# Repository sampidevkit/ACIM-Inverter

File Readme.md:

# AC INDUCTION MOTOR - INVERTER BOARD V2

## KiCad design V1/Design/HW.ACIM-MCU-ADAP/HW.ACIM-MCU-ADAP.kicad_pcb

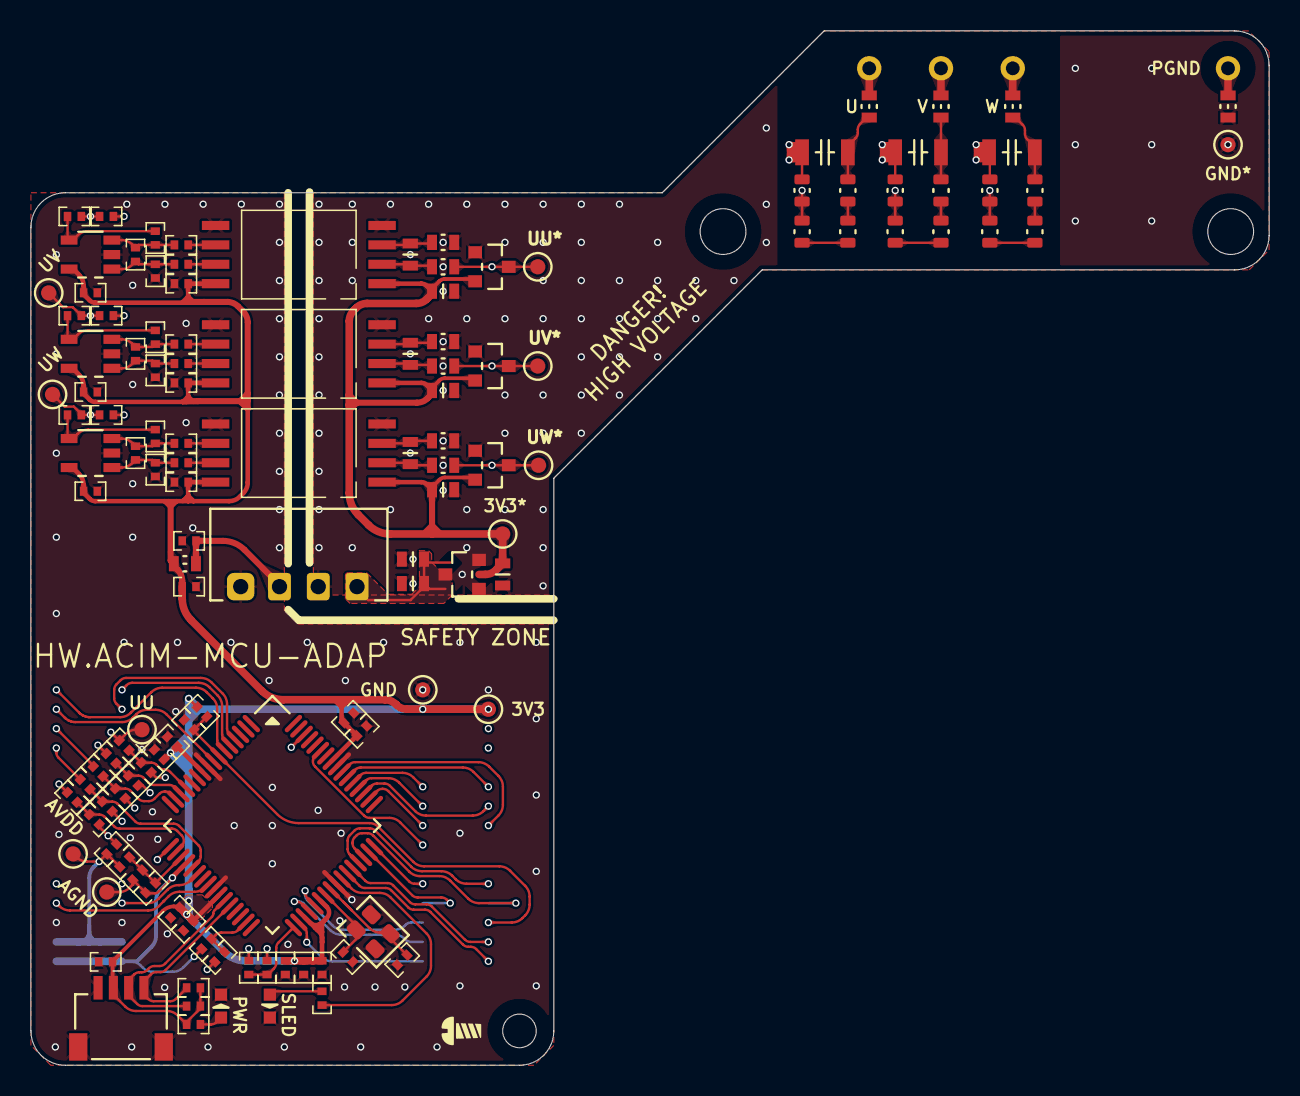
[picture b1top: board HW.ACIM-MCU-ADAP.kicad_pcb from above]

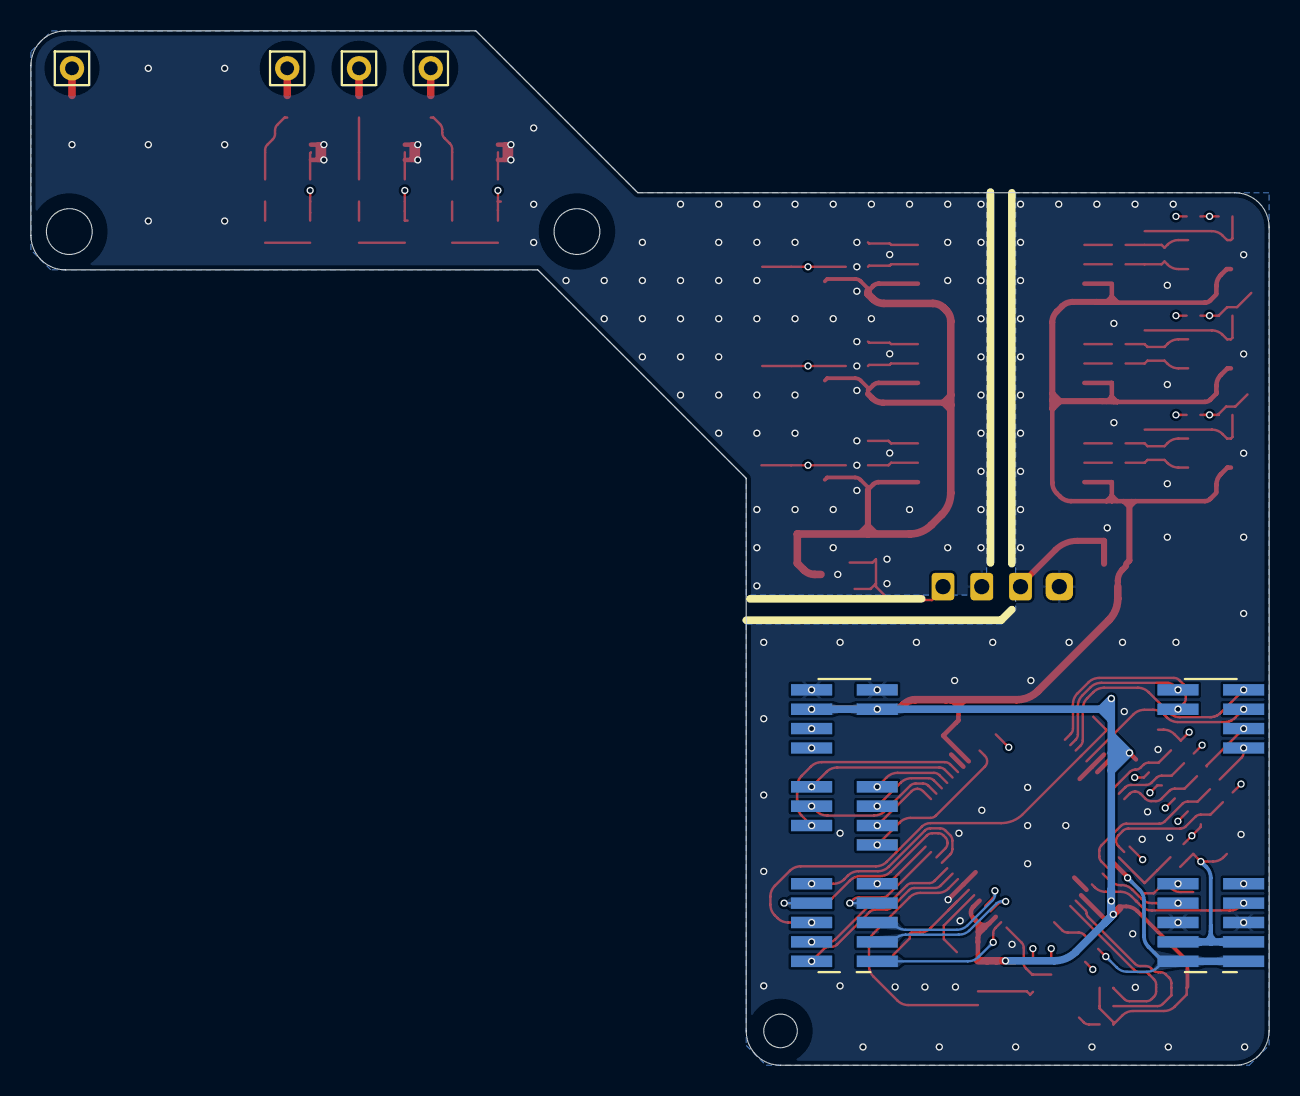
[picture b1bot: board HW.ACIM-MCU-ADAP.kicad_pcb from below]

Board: 4 copper layers, 81.1 x 67.8 mm, 137 parts (6 on the bottom side), 92 nets.

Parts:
C1, C2, C10: 100pF/2kV; CAP1206
C3, C4, C65: 1nF; CAP0603
C5, C6, C18, C67: 100nF; CAP0603
C7, C8, C12, C13, C20, C69, C73, C110, C112, C121, C123, C125, C127: 100nF; CAP0402
C9, C11, C14, C15, C21, C22, C23, C24, C25, C26, C27, C28, C71, C74: 1nF; CAP0402
C16, C17: 10uF; CAP0603
C19, C29, C113, C122, C124, C126, C128: 10uF; CAP0402
C101, C119, C120: 22pF; CAP0402
D1, D2, D14: BAV99; SOT23
D101: SLED; LED0603
D102: PWR; LED0603
FT1, FT2, FT3, FT4, FT5: 1K@100MHz; FT0603
FT6, FT7, FT8, FT9, FT10, FT11, FT12, FT13: 1K@100MHz; IND0402
J1: U; SIL01
J2: V; SIL01
J3: W; SIL01
J4: PGND; SIL01
J5: QWIIC; HDM-1x4x1.0-RA
J101, J102: HEADER 2x15POS; HD-2x15x1.27-SMD
MD1: 3.3V-5V/1W; B1524S-1WR3
R1, R2, R3, R5, R6, R7, R27, R28, R29: 100K, 1%; RES0603
R4, R8, R30: 100R, 1%; RES0603
R9, R10, R11, R12, R33, R34: 10R, 1%; RES0603
R13, R14, R15, R16, R37, R38: 10K, 1%; RES0402
R17, R18, R19, R20, R39, R40: 4.99K, 1%; RES0402
R21, R22, R41: 10R, 1%; RES0402
R23, R24: 2.2K; RES0402
R101, R102: 1K; RES0402
R103: 10K; RES0402
SH5, SH7, SH8: SCREW HOLDER; SCREWHOLE-2.5M
TP1: UU; TP1MM
TP2: UV; TP1MM
TP3: UW; TP1MM
TP4: GND*; TP1MM
TP5: 3V3*; TP1MM
TP6: UU*; TP1MM
TP7: UV*; TP1MM
TP8: UW*; TP1MM
TP101: GND; TP1MM
TP102: 3V3; TP1MM
TP103: AGND; TP1MM
TP104: AVDD; TP1MM
U1, U2, U15: ISO OPAMP 1-CH; SOIC8-11.5
U3, U4, U17: OP-1CH; SOT-23-5_MCHP
U5: LDO 3.3V; SOT23
U101: MIPS 32-bit DSC; TQFP64_10x10_MCHP
U102: 24MHz; SMD4-2520

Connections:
+3V3_ISO: C5.1, C6.1, C16.1, C67.1, D1.2 (K2), D2.2 (K2), D14.2 (K2), TP5.1, U1.1 (VDD1), U2.1 (VDD1), U5.2 (VIN), U15.1 (VDD1)
+3V3_MCU: C7.1, C8.1, C12.2, C13.2, C20.1, C29.2, C69.1, C73.2, C110.2, C121.2, C122.2, C123.2, C124.2, C125.2, C126.2, C127.2, C128.2, FT5.2, J5.2 (VDD), J102.27, J102.28, R23.2, R24.2, R102.2, R103.2, TP102.1, U1.8 (VDD2), U2.8 (VDD2), U3.5 (VDD), U4.5 (VDD), U15.8 (VDD2), U17.5 (VDD), U101.10 (VDD1), U101.26 (VDD2), U101.35 (VUSB3V3), U101.38 (VDD3), U101.57 (VDD4)
/MCU/DB_RXD: J102.7, U101.47 (SOSCI/RPC13/RC13)
/MCU/DB_TXD: J102.8, U101.46 (OA5OUT/AN25/CVD25/C5IN4-/RPB7/SCK1/INT0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)
/MCU/DEV_RELAY: J101.10, U101.17 (PGC1/OA1IN+/AN4/C1IN1+/C1IN3-/C2IN3-/RP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)
/MCU/DV_RXD: J102.9, U101.48 (SOSCO/T1CK/RPB8/RB8)
/MCU/DV_TXD: J102.10, U101.45 (DAC2/AN48/CVD48/RPC10/PMA14/PMCS/RC10)
/MCU/ENC_A: J101.28, U101.4 (AN19/CVD19/RPG6/PWM10L/PMA5/RG6)
/MCU/ENC_B: J101.30, U101.5 (AN18/CVD18/RPG7/PWM10H/SCL1/PMA4/RG7)
/MCU/ENC_HOME: J101.27, U101.8 (AN16/CVD16/RPG9/PMA2/RG9)
/MCU/ENC_IDX: J101.29, U101.6 (AN17/CVD17/RPG8/SDA1/PMA3/RG8)
/MCU/IDC: FT6.1, J101.25
/MCU/IDC_SEN: C21.2, FT6.2, U101.15 (PGD3/VREF-/OA2IN-/AN2/C2IN1-/RPB0/CTED2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)
/MCU/IND_ERR: J101.8, U101.22 (OA3IN-/AN7/CVD7/C3IN1-/C4IN1-/RPC1/PMA7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)
/MCU/IND_RUN: J101.7, U101.24 (AN11/CVD11/C1IN2-/FLT4/PMA12/RC11)
/MCU/MC_IU: FT8.1, J102.24
/MCU/MC_IU_SEN: C23.2, FT8.2, U101.33 (OA5IN+/DAC1/AN24/CVD24/C5IN1+/C5IN3-/RP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)
/MCU/MC_IW: FT9.1, J102.26
/MCU/MC_IW_SEN: C24.2, FT9.2, U101.31 (TDI/DAC3/AN26/CVD26/RPA8/SDA2/PMA9/RA8)
/MCU/MC_PWM_UH: J102.19, U101.53 (TRD2/RPD5/PWM12H/PMRD/RD5)
/MCU/MC_PWM_UL: J102.20, U101.54 (TRD3/RPD6/PWM12L/RD6)
/MCU/MC_PWM_VH: J102.17, U101.52 (TRD1/RPC8/PWM5H/PMWR/RC8)
/MCU/MC_PWM_VL: J102.16, U101.55 (RPC9/PWM11H/PWM5L/RC9)
/MCU/MC_PWM_WH: J102.15, U101.50 (TRCLK/RPC6/PWM6H/RC6)
/MCU/MC_PWM_WL: J102.18, U101.51 (TRD0/RPC7/PWM12H/PWM6L/RC7)
/MCU/MC_UU: C74.2, FT10.1, R41.1, TP1.1
/MCU/MC_UU_DIV: C25.2, FT10.2, U101.13 (OA2OUT/AN0/C2IN4-/C4IN3-/RPA0/RA0)
/MCU/MC_UV: C14.2, FT11.1, R21.1, TP2.1
/MCU/MC_UV_DIV: C26.2, FT11.2, U101.14 (OA2IN+/AN1/C2IN1+/RPA1/RA1)
/MCU/MC_UW: C15.2, FT12.1, R22.1, TP3.1
/MCU/MC_UW_DIV: C27.2, FT12.2, U101.18 (PGD1/OA1IN-/AN5/CTCMP/C1IN1-/RTCC/RPB3/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)
/MCU/PGC: J102.4, U101.44 (PGC2/RPB6/SCL3/SCK2/PMA15/RB6)
/MCU/PGD: J102.2, U101.43 (PGD2/RPB5/SDA3/USBID1/RB5)
/MCU/PWR_RELAY: J101.9, U101.62 (RPB12/PWM2H/PMD2/RB12)
/MCU/SCL: J5.4 (SCL), R23.1, U101.28 (AN13/CVD13/C3IN2-/FLT6/SCL4/PMA10/RE13)
/MCU/SDA: J5.3 (SDA), R24.1, U101.27 (AN12/CVD12/C2IN2-/C5IN2-/SDA4/FLT5/PMA1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)
/MCU/SLED: R101.2, U101.42 (RD8)
/MCU/UDC: FT7.1, J101.23
/MCU/UDC_DIV: C22.2, FT7.2, U101.21 (OA3OUT/AN6/CVD6/C3IN4-/C4IN1+/C4IN4-/RP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)
/MCU/USB_N: J102.3, U101.36 (D-)
/MCU/USB_P: J102.5, U101.37 (D+)
/MCU/VBUS: J102.1, U101.34 (VBUS)
/MCU/~INV_FLT: J102.13, U101.59 (RPF1/PWM11L/RF1)
/MCU/~MCLR: C101.2, J102.6, R103.1, U101.7 (~MCLR)
AGND_MCU: C14.1, C15.1, C21.1, C22.1, C23.1, C24.1, C25.1, C26.1, C27.1, C28.1, C74.1, C112.1, C113.1, J101.1, J101.2, TP103.1, U101.20 (AVSS)
AVDD_MCU: C28.2, FT13.2, J101.3, J101.4, TP104.1
GND_ISO: C1.2, C2.2, C5.2, C6.2, C10.2, C16.2, C17.2, C18.2, C67.2, D1.1 (A1), D2.1 (A1), D14.1 (A1), FT4.2, MD1.3 (DC-), R4.2, R8.2, R10.2, R12.2, R30.2, R34.2, TP4.1, U1.4 (GND1), U2.4 (GND1), U5.1 (GND), U15.4 (GND1)
GND_MCU: C7.2, C8.2, C12.1, C13.1, C19.2, C20.2, C29.1, C69.2, C73.1, C101.1, C110.1, C119.1, C120.1, C121.1, C122.1, C123.1, C124.1, C125.1, C126.1, C127.1, C128.1, D101.K, D102.K, J5.0 (EP), J5.1 (GND), J101.5, J101.6, J102.29, J102.30, MD1.1 (VI-), R17.2, R18.2, R39.2, TP101.1, U1.5 (GND2), U2.5 (GND2), U3.2 (VSS), U4.2 (VSS), U15.5 (GND2), U17.2 (VSS), U101.9 (VSS1), U101.25 (VSS2), U101.41 (VSS3), U101.56 (VSS4), U102.2 (GND1), U102.4 (GND2)
unnamed: C1.1, FT2.2, R1.1
unnamed: C2.1, FT3.2, R5.1
unnamed: C10.1, FT1.2, R27.1
unnamed: D1.3 (COM), R3.2, R4.1, R9.2, TP7.1
unnamed: D2.3 (COM), R7.2, R8.1, R11.2, TP8.1
unnamed: D14.3 (COM), R29.2, R30.1, R33.2, TP6.1
unnamed: D101.A, R101.1
unnamed: D102.A, R102.1
unnamed: FT1.1, J1.1
unnamed: FT2.1, J2.1
unnamed: FT3.1, J3.1
unnamed: FT4.1, J4.1
unnamed: C17.1, C18.1, MD1.4 (DC+), U5.3 (VOUT)
unnamed: C19.1, FT5.1, MD1.2 (VI+)
unnamed: R1.2, R2.1
unnamed: R2.2, R3.1
unnamed: R5.2, R6.1
unnamed: R6.2, R7.1
unnamed: R27.2, R28.1
unnamed: R28.2, R29.1
unnamed: C3.2, R9.1, U1.2 (VIN+)
unnamed: C3.1, R10.1, U1.3 (VIN-)
unnamed: R13.2, U1.7 (VOUT+)
unnamed: R14.2, U1.6 (VOUT-)
unnamed: C4.2, R11.1, U2.2 (VIN+)
unnamed: C4.1, R12.1, U2.3 (VIN-)
unnamed: R15.2, U2.7 (VOUT+)
unnamed: R16.2, U2.6 (VOUT-)
unnamed: C9.2, R13.1, R17.1, U3.1 (IN+)
unnamed: C9.1, R14.1, R19.1, U3.3 (IN-)
unnamed: R19.2, R21.2, U3.4 (OUT)
unnamed: C11.2, R15.1, R18.1, U4.1 (IN+)
unnamed: C11.1, R16.1, R20.1, U4.3 (IN-)
unnamed: R20.2, R22.2, U4.4 (OUT)
unnamed: C65.2, R33.1, U15.2 (VIN+)
unnamed: C65.1, R34.1, U15.3 (VIN-)
unnamed: R37.2, U15.7 (VOUT+)
unnamed: R38.2, U15.6 (VOUT-)
unnamed: C71.2, R37.1, R39.1, U17.1 (IN+)
unnamed: C71.1, R38.1, R40.1, U17.3 (IN-)
unnamed: R40.2, R41.2, U17.4 (OUT)
unnamed: C112.2, C113.2, FT13.1, U101.19 (AVDD)
unnamed: C119.2, U101.39 (OSCI/CLKI/AN49/CVD49/RPC12/RC12), U102.1 (X1)
unnamed: C120.2, U101.40 (OSCO/CLKO/RPC15/RC15), U102.3 (X2)

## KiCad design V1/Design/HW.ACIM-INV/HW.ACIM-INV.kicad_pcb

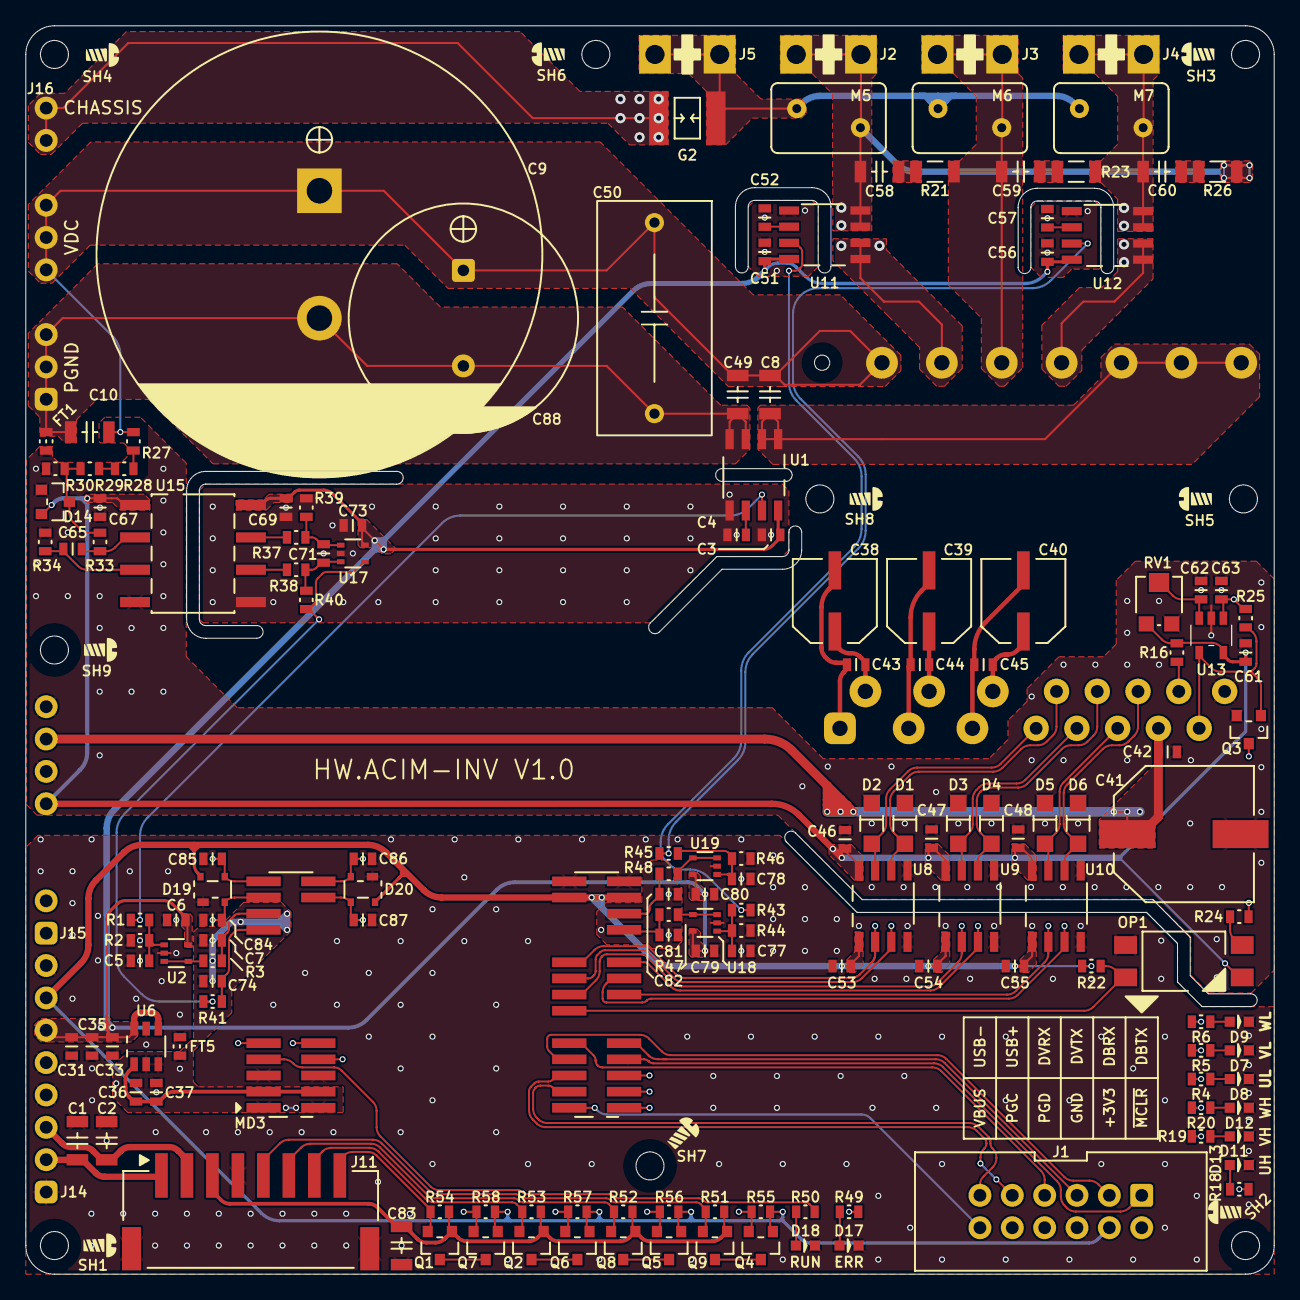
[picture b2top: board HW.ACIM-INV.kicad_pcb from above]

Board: 4 copper layers, 98.0 x 98.0 mm, 169 parts (1 on the bottom side), 108 nets.

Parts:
C1, C2, C83: 10uF/35V; CAP1206
C3, C6, C35, C36, C42, C43, C44, C45, C51, C56, C61, C62, C63, C67, C69, C73, C79, C80: 100nF; CAP0603
C4, C5, C7, C52, C57, C65, C71, C74, C77, C78, C81, C82: 1nF; CAP0603
C8, C10, C49, C58, C59, C60: 100pF/2kV; CAP1206
C9: 680uF/450V; ESMQ451VSN681MA50S
C31, C37, C46, C47, C48, C53, C54, C55: 10uF; CAP0603
C33, C84, C85, C86, C87: 22pF; CAP0603
C38, C39, C40: 47uF/35V; CAP_ELEC-6.6x6.6-DIA6.3
C41: 470uF/25V; CAP_ELEC-10.3x10.3-DIA10
C50: 470nF/630V; FCAP-15MM
C88: 100uF/450V; CAP_ELEC-18.0x51.5-LS7.5
D1, D2, D3, D4, D5, D6: 5VZ; SOD-123FL_12
D7: VL; LED0603
D8: UL; LED0603
D9: WL; LED0603
D11: VH; LED0603
D12: WH; LED0603
D13: UH; LED0603
D14: GP DIODE; SOT23
D17: ERR; LED0603
D18: RUN; LED0603
D19, D20: TVS 5.5V; SOT143B_NEXT
FT1, FT5: 120R@100MHz; FT0603
G2: 300V; GDT1812_3532
J1: MCDBG; IDC-2x6x2.54MM_TH
J2: U; QC-6.3
J3: V; QC-6.3
J4: W; QC-6.3
J5: N; QC-6.3
J11: ENCODER; HDM1x8x2.0_SMA_RA
J14: MCU PWR; HDM1x8x2.54_TH_RA
J15: INV PWR & RELAYS; HDM1x8x2.54_TH_RA
J16: HIGH VOLTAGE OUTPUTS; HDF1x10x2.54_TH_RA
M5, M6, M7: 560V/1.75kA; MOV5MM
MD3: ACIM-MCU; HW.ACIM-MCU_SMD
OP1: OPTO-BJT-1CH; OPTO_SO4_7.6MM
Q1, Q2, Q4, Q5, Q6, Q7, Q8, Q9: 60V/265mA; SOT23
Q3: 20V/1A; SOT23
R1, R2, R27, R28, R29, R43, R44, R45, R46: 100K, 1%; RES0603
R3, R33, R34, R41, R47, R48: 10R, 1%; RES0603
R4, R5, R6, R18, R19, R20, R24, R49, R50: 1K; RES0603
R16, R22: 10K; RES0603
R21, R23, R26: 4.7R; RES1206
R25: 1.2M; RES0603
R30: 1.1K, 1%; RES0603
R37, R38: 10K, 1%; RES0603
R39, R40: 4.99K, 1%; RES0603
R51, R52, R53, R54, R55, R56, R57, R58: 2.2K; RES0603
RV1: 20K; TC33X-2
SH1, SH2, SH3, SH4, SH5, SH6, SH7, SH8, SH9: SCREW HOLDER; SCREWHOLE-2.5M
U1, U11, U12: I=±10A; SOIC8_ALL
U2, U17, U18, U19: OP-1CH; SOT353
U6: LDO 3.3V±0.1%/20mA; SOT-23-6_MCHP
U7: IPM 600V/15A; CIPOS-MINI
U8, U9, U10: DIGI ISO; SOIC8_ALL
U13: CMP-1CH; SOT25_DIODES
U15: ISO OPAMP 1-CH; SOP8-2.54

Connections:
+3V3_ADC: C36.2, C37.2, MD3.L3 (AVDD), MD3.L4 (AVDD), U6.1 (OUT)
+3V3_MCU: C53.2, C54.2, C55.2, D19.4 (CH3), D20.4 (CH3), J1.4 (VDD), J14.7, MD3.R27 (+3V3), MD3.R28 (+3V3), Q4.1 (G), Q5.1 (G), Q6.1 (G), Q7.1 (G), R22.1, R55.1, R56.1, R57.1, R58.1, U8.1 (VDD1), U9.1 (VDD1), U10.1 (VDD1)
+5V_INV: C46.2, C47.2, C48.2, C61.2, C67.1, D14.2 (K2), J15.5, OP1.1 (A), R16.1, RV1.1 (CCW), U8.8 (VDD2), U9.8 (VDD2), U10.8 (VDD2), U13.5 (VDD), U15.1 (VDD1)
+5V_MCU: C3.2, C6.2, C31.2, C33.2, C35.2, C51.2, C56.2, C69.1, C73.2, C79.2, C80.2, J14.6, U1.8 (VCC), U2.5 (VDD), U6.4 (~SHDN), U6.6 (VDD), U11.8 (VCC), U12.8 (VCC), U15.8 (VDD2), U17.5 (VDD), U18.5 (VDD), U19.5 (VDD)
+12V_MCU: C2.2, J11.2, J14.3
+16V_INV: C41.+, C42.1, J15.7, U7.13 (VDD)
+24V_MCU: C1.2, J11.1, J14.2
/ENCODER/ENC_A: C87.2, D20.3 (CH2), MD3.L28 (ENC_A), Q7.2 (S), R58.2
/ENCODER/ENC_B: C86.2, D20.2 (CH1), MD3.L30 (ENC_B), Q6.2 (S), R57.2
/ENCODER/ENC_HOME: C84.2, D19.2 (CH1), MD3.L27 (ENC_HOME), Q4.2 (S), R55.2
/ENCODER/ENC_INDEX: C85.2, D19.3 (CH2), MD3.L29 (ENC_IDX), Q5.2 (S), R56.2
/ENCODER/HOME: J11.5, Q9.2 (S), R51.2
/ENCODER/INDEX: J11.6, Q8.2 (S), R52.2
/ENCODER/PULSE_A: J11.8, Q1.2 (S), R54.2
/ENCODER/PULSE_B: J11.7, Q2.2 (S), R53.2
/ENCODER/V_ENC: C83.2, J11.3, Q1.1 (G), Q2.1 (G), Q8.1 (G), Q9.1 (G), R51.1, R52.1, R53.1, R54.1
/INVERTER/IPM_PWM_FLT: Q3.1 (G), R25.2, U7.15 (ITR), U13.4 (VOUT)
/INVERTER/IPM_PWM_UH: D2.1, U7.7 (HINU), U8.7 (VOA)
/INVERTER/IPM_PWM_UL: D4.1, U7.10 (LINU), U9.6 (VOB)
/INVERTER/IPM_PWM_VH: D1.1, U7.8 (HINV), U8.6 (VOB)
/INVERTER/IPM_PWM_VL: D5.1, U7.11 (LINV), U10.7 (VOA)
/INVERTER/IPM_PWM_WH: D3.1, U7.9 (HINW), U9.7 (VOA)
/INVERTER/IPM_PWM_WL: D6.1, U7.12 (LINW), U10.6 (VOB)
/INVERTER/IPM_TEMP_SEN: C63.2, R16.2, R25.1, U7.14 (VFO), U13.1 (VIN-)
/INVERTER/MC_IDC_HAL: R1.1, U1.7 (VIOUT)
/INVERTER/MC_IU_HAL: R43.1, U11.7 (VIOUT)
/INVERTER/MC_IV_HAL: R45.1, U12.7 (VIOUT)
/INVERTER/MC_PWM_UH: MD3.R19 (MC_PWM_UH), R18.2, U8.2 (VIA)
/INVERTER/MC_PWM_UL: MD3.R20 (MC_PWM_UL), R4.2, U9.3 (VIB)
/INVERTER/MC_PWM_VH: MD3.R17 (MC_PWM_VH), R19.2, U8.3 (VIB)
/INVERTER/MC_PWM_VL: MD3.R16 (MC_PWM_WL), R5.2, U10.2 (VIA)
/INVERTER/MC_PWM_WH: MD3.R15 (MC_PWM_WH), R20.2, U9.2 (VIA)
/INVERTER/MC_PWM_WL: MD3.R18 (MC_PWM_VL), R6.2, U10.3 (VIB)
/INVERTER/MC_TEMP_FLT: MD3.R13 (~MC_PWM_FLT), OP1.4 (C), R22.2
/INVERTER/MC_U: C58.1, J2.1, M5.2, R26.2, U11.3 (IPN1), U11.4 (IPN2)
/INVERTER/MC_V: C59.2, J3.1, M6.2, R21.2, U7.21 (V)
/INVERTER/MC_W: C60.1, J4.1, M7.2, R23.2, U12.3 (IPN1), U12.4 (IPN2)
/MCU POWER/PWR_RELAY: J15.2, MD3.L9 (PWR_RELAY)
/MCU POWER/~DEV_RELAY: J15.1, MD3.L10 (~DEV_RELAY)
/MCU/DB_RXD: J1.3 (DB_RXD), MD3.R7 (DB_RXD)
/MCU/DB_TXD: J1.1 (DB_TXD), MD3.R8 (DB_TXD)
/MCU/DV_RXD: J1.7 (DV_RXD), MD3.R9 (DV_RXD)
/MCU/DV_TXD: J1.5 (DV_TXD), MD3.R10 (DV_TXD)
/MCU/IND_ERR: MD3.L8 (IO2), R49.1
/MCU/IND_RUN: MD3.L7 (IO1), R50.1
/MCU/MC_IDC_SEN: C7.2, MD3.L25 (IDC_SEN), R3.1
/MCU/MC_IU_SEN: C81.2, MD3.R24 (MC_IU_SEN), R47.1
/MCU/MC_IV_SEN: C82.2, MD3.R26 (MC_IV_SEN), R48.1
/MCU/MC_UDC_DIV: C74.2, MD3.L23 (UDC_DIV), R41.1
/MCU/PGC: J1.10 (PGC/SWDCK), MD3.R4 (PGC)
/MCU/PGD: J1.8 (PGD/SWDIO), MD3.R2 (PGD)
/MCU/USB_N: J1.11 (USB_DM), MD3.R3 (USB_N)
/MCU/USB_P: J1.9 (UDB_DP), MD3.R5 (USB_P)
/MCU/VBUS: J1.12 (VBUS), MD3.R1 (VBUS)
/MCU/~MCLR: J1.2 (~RESET), MD3.R6 (~MCLR)
CHASSIS: G2.2, J16.9, J16.10
GND_ADC: C7.1, C36.1, C37.1, C74.1, C81.1, C82.1, FT5.2, MD3.L1 (AGND), MD3.L2 (AGND), U6.2 (GND3), U6.3 (GND1)
GND_INV: C41.-, C42.2, C46.1, C47.1, C48.1, C61.1, C62.1, C63.1, C67.2, D1.2, D2.2, D3.2, D4.2, D5.2, D6.2, D14.1 (A1), FT1.1, J15.6, J15.8, Q3.2 (S), R30.2, R34.2, RV1.3 (CW), U7.16 (VSS), U8.5 (GND2), U9.5 (GND2), U10.5 (GND2), U13.2 (VSS), U15.4 (GND1)
GND_MCU: C1.1, C2.1, C3.1, C4.1, C5.1, C6.1, C31.1, C33.1, C35.1, C51.1, C52.1, C53.1, C54.1, C55.1, C56.1, C57.1, C69.2, C73.1, C77.1, C78.1, C79.1, C80.1, C83.1, C84.1, C85.1, C86.1, C87.1, D7.K, D8.K, D9.K, D11.K, D12.K, D13.K, D17.K, D18.K, D19.1 (GND), D20.1 (GND), FT5.1, J1.6 (GND), J11.4, J11.9, J14.1, J14.4, J14.5, J14.8, MD3.L5 (GND), MD3.L6 (GND), MD3.R29 (GND), MD3.R30 (GND), OP1.3 (E), R2.2, R39.2, R44.2, R46.2, U1.5 (GND), U2.2 (VSS), U6.5 (GND2), U8.4 (GND1), U9.4 (GND1), U10.4 (GND1), U11.5 (GND), U12.5 (GND), U15.5 (GND2), U17.2 (VSS), U18.2 (VSS), U19.2 (VSS)
unnamed: C58.2, R21.1
unnamed: C59.1, R23.1
unnamed: C60.2, R26.1
unnamed: D7.A, R5.1
unnamed: D8.A, R4.1
unnamed: D9.A, R6.1
unnamed: D11.A, R19.1
unnamed: D12.A, R20.1
unnamed: D13.A, R18.1
unnamed: D14.3 (COM), R29.2, R30.1, R33.2
unnamed: D17.A, R49.2
unnamed: D18.A, R50.2
unnamed: G2.1, J5.1, M5.1, M6.1, M7.1
unnamed: OP1.2 (K), R24.2
unnamed: Q1.3 (D), Q7.3 (D)
unnamed: Q2.3 (D), Q6.3 (D)
unnamed: Q3.3 (D), R24.1
unnamed: Q4.3 (D), Q9.3 (D)
unnamed: Q5.3 (D), Q8.3 (D)
unnamed: R27.2, R28.1
unnamed: R28.2, R29.1
unnamed: C62.2, RV1.2 (WIPER), U13.3 (VIN+)
unnamed: C4.2, U1.6 (FILTER)
unnamed: C8.2, U1.1 (IPP1), U1.2 (IPP2), U7.17 (NW), U7.18 (NV), U7.19 (NU)
unnamed: C5.2, R1.2, R2.1, U2.1 (IN+)
unnamed: R3.2, U2.3 (IN-), U2.4 (OUT)
unnamed: C38.+, C43.1, U7.2 (VBU)
unnamed: C39.+, C44.1, U7.4 (VBV)
unnamed: C40.+, C45.1, U7.6 (VBW)
unnamed: C38.-, C43.2, U7.1 (VSU)
unnamed: C39.-, C44.2, U7.3 (VSV)
unnamed: C40.-, C45.2, U7.5 (VSW)
unnamed: C52.2, U11.6 (FILTER)
unnamed: U7.22 (U), U11.1 (IPP1), U11.2 (IPP2)
unnamed: C57.2, U12.6 (FILTER)
unnamed: U7.20 (W), U12.1 (IPP1), U12.2 (IPP2)
unnamed: C65.2, R33.1, U15.2 (VIN+)
unnamed: C65.1, R34.1, U15.3 (VIN-)
unnamed: R37.2, U15.7 (VOUT+)
unnamed: R38.2, U15.6 (VOUT-)
unnamed: C71.2, R37.1, R39.1, U17.1 (IN+)
unnamed: C71.1, R38.1, R40.1, U17.3 (IN-)
unnamed: R40.2, R41.2, U17.4 (OUT)
unnamed: C77.2, R43.2, R44.1, U18.1 (IN+)
unnamed: R47.2, U18.3 (IN-), U18.4 (OUT)
unnamed: C78.2, R45.2, R46.1, U19.1 (IN+)
unnamed: R48.2, U19.3 (IN-), U19.4 (OUT)
PGND: C9.-, C10.2, C49.2, C50.2, C88.-, FT1.2, J16.1, J16.2, J16.3, U1.3 (IPN1), U1.4 (IPN2)
VDC: C8.1, C9.+, C10.1, C49.1, C50.1, C88.+, J16.5, J16.6, J16.7, R27.1, U7.23

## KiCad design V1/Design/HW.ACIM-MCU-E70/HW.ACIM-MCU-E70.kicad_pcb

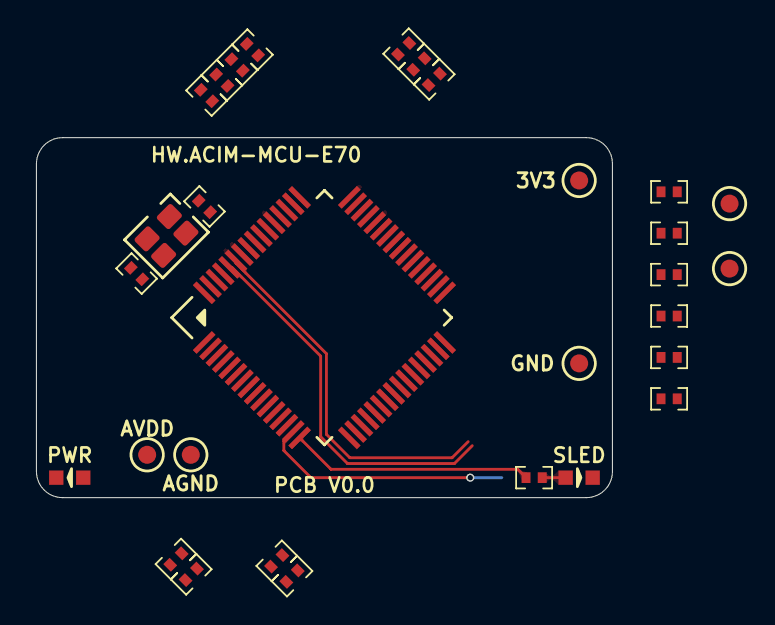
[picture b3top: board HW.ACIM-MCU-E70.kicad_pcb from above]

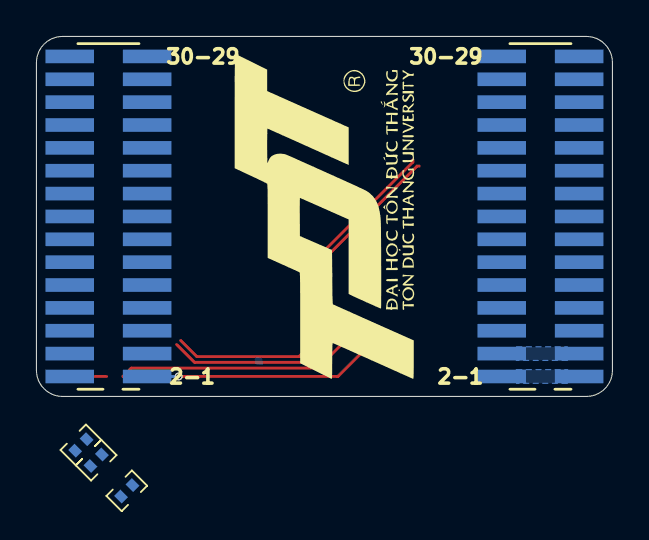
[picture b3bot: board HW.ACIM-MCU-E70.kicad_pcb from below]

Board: 4 copper layers, 32.0 x 20.0 mm, 35 parts (5 on the bottom side), 39 nets.

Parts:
C1, C19, C20: 22pF; CAP0402
C2, C4, C5, C6, C10, C12, C21, C23, C25, C27: 100nF; CAP0402
C3: 2.2uF; CAP0402
C13, C28: 10uF; CAP0402
D1: SLED; LED0603
D2: PWR; LED0603
FT1, FT2: 1K@100MHz; IND0402
J1, J2: HEADER 2x15POS; HD-2x15x1.27-SMD
R1, R2, R5: 1K; RES0402
R3, R4: 10K; RES0402
TP1: GND; TP1MM
TP2: 3V3; TP1MM
TP3: AGND; TP1MM
TP4: AVDD; TP1MM
TP5: ERASE; TP1MM
TP6: VCORE; TP1MM
U1: ATSAME70J20B; TQFP64_10x10_MCHP
U2: 12MHz; SMD4-2520

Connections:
+3V3: C12.2, C13.2, C21.2, C23.2, C25.2, J2.27, J2.28, R2.2, R3.2, TP2.1, U1.4 (VDDIN), U1.10 (VDDIO), U1.42 (VDDIO), U1.58 (VDDIO), U1.64 (VDDPLLUSB)
/DB_RXD: J2.7, U1.33 (PA9/PWM0.F0/URXD0)
/DB_TXD: J2.8, U1.28 (PA10/UTXD0)
/DV_CTS: J2.12, R5.1
/DV_RTS: J2.11, R5.2
/DV_RXD: J2.9, U1.32 (PA5/PWM1.L3/URXD1)
/DV_TXD: J2.10, U1.34 (PA4/SCL0/UTXD1)
/ENC_A: J1.28, U1.26 (PD21/PWM0.H1/QEI3A)
/ENC_B: J1.30, U1.25 (PD22/PWM0.H2/QEI3B)
/IDC_SEN: J1.25, U1.11 (PB3/AD0.2/USRTS0)
/MC_IU_SEN: J2.24, U1.8 (PB0/AD0.10/PWM0.H0/USRXD0)
/MC_IV_SEN: J2.26, U1.12 (PA21/AD0.1/PWM1.F0/USRXD1)
/MC_PWM_UH: J2.19, U1.27 (PA11/PWM0.H0/PWM1.L0/~QSPI_CS)
/MC_PWM_UL: J2.20, U1.22 (PD24/PWM0.L0)
/MC_PWM_VH: J2.17, U1.29 (PA12/PWM0.H1/PWM1.H0/QSPI_MISO)
/MC_PWM_VL: J2.18, U1.20 (PD25/PWM0.L1/URXD2)
/MC_PWM_WH: J2.15, U1.18 (PA13/PWM0.H2/PWM1.L1/QSPI_MOSI)
/MC_PWM_WL: J2.16, U1.21 (PD26/PWM0.L2/UTXD1/UTXD2)
/MC_VR_DIV: J2.22, U1.7 (PB1/AD1.0/PWM0.H1/USTXD0)
/SCL: J1.11, U1.47 (PB5/PWM0.L0/SCL1)
/SDA: J1.12, U1.46 (PB4/PWM0.H2/SDA1/USTXD1)
/SLED: R1.2, U1.16 (PA8/PWM1.H3/XOUT32)
/SWDCLK: J2.4, U1.39 (PB7/SWDCLK)
/SWDIO: J2.2, U1.35 (PB6/SWDIO)
/USB_N: J2.3, U1.59 (DM)
/USB_P: J2.5, U1.60 (DP)
/USB_VBUS: J2.1, U1.15 (PA7/PWM0.H3/XIN32)
/VDC_DIV: J1.23, U1.9 (PB2/AD0.5/USCTS0)
/~MCLR: C1.2, J2.6, R3.1, U1.36 (NRST)
AGND: C27.1, C28.1, FT2.1, J1.1, J1.2, TP3.1
AVDD: C27.2, C28.2, J1.3, J1.4, TP4.1, U1.5 (VREFP)
GND: C1.1, C2.1, C3.1, C4.1, C5.1, C6.1, C10.1, C12.1, C13.1, C19.1, C20.1, C21.1, C23.1, C25.1, D1.K, D2.K, FT2.2, J1.5, J1.6, J2.29, J2.30, R4.1, TP1.1, U1.6 (GND), U1.14 (GND), U1.31 (GND), U2.2 (GND1), U2.4 (GND2)
unnamed: D1.A, R1.1
unnamed: D2.A, R2.1
unnamed: C19.2, U1.62 (PB8/XOUT), U2.1 (X1)
unnamed: C20.2, U1.63 (PB9/XIN), U2.3 (X2)
unnamed: R4.2, TP5.1, U1.38 (PB12/PWM0.L1/ERASE)
unnamed: C2.2, C3.2, C4.2, C6.2, C10.2, FT1.2, TP6.1, U1.3 (VDDOUT), U1.13 (VDDCORE), U1.24 (VDDCORE), U1.61 (VDDCORE)
unnamed: C5.2, FT1.1, U1.52 (VDDPLL)

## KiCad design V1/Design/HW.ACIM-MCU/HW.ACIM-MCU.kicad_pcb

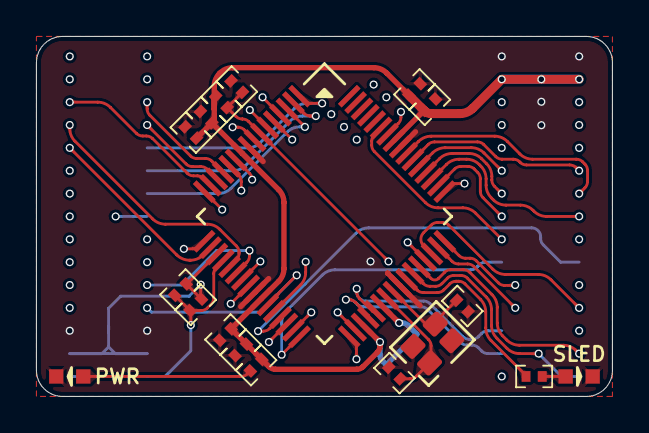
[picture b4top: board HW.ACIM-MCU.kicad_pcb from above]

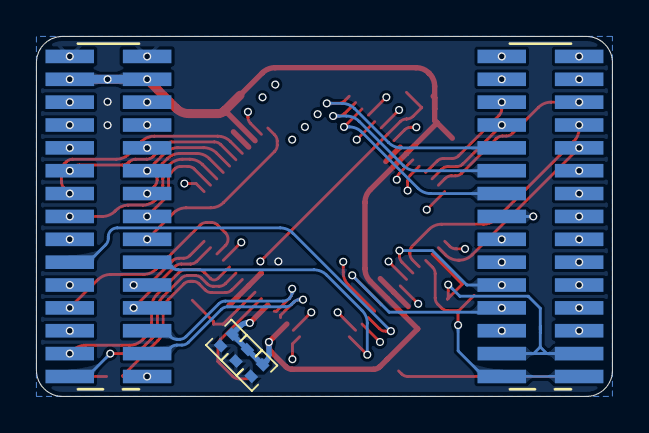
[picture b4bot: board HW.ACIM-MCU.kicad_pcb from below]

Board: 4 copper layers, 32.0 x 20.0 mm, 23 parts (5 on the bottom side), 59 nets.

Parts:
C1, C19, C20: 22pF; CAP0402
C10, C12, C21, C23, C25, C27: 100nF; CAP0402
C13, C22, C24, C26, C28: 10uF; CAP0402
D1: SLED; LED0603
D2: PWR; LED0603
J1, J2: HEADER 2x15POS; HD-2x15x1.27-SMD
R1, R2: 1K; RES0402
R3: 10K; RES0402
U1: MIPS 32-bit DSC; TQFP64_10x10_MCHP
U2: 12MHz; SMD4-2520

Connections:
+3V3: C10.2, C21.2, C22.2, C23.2, C24.2, C25.2, C26.2, C27.2, C28.2, J2.27, J2.28, R2.2, R3.2, U1.10 (VDD1), U1.26 (VDD2), U1.35 (VUSB3V3), U1.38 (VDD3), U1.57 (VDD4)
/CTS2: J2.12, U1.29 (AN14/CVD14/RPE14/FLT7/PMA1/RE14)
/ENC_A: J1.28, U1.4 (AN19/CVD19/RPG6/PWM10L/PMA5/RG6)
/ENC_B: J1.30, U1.5 (AN18/CVD18/RPG7/PWM10H/SCL1/PMA4/RG7)
/ENC_HOME: J1.27, U1.8 (AN16/CVD16/RPG9/PMA2/RG9)
/ENC_IDX: J1.29, U1.6 (AN17/CVD17/RPG8/SDA1/PMA3/RG8)
/IDC_SEN: J1.25, U1.15 (PGD3/VREF-/OA2IN-/AN2/C2IN1-/RPB0/CTED2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)
/IO00: J2.14, U1.58 (RPF0/PWM11H/RF0)
/IO01: J1.7, U1.28 (AN13/CVD13/C3IN2-/FLT6/SCL4/PMA10/RE13)
/IO02: J1.8, U1.27 (AN12/CVD12/C2IN2-/C5IN2-/SDA4/FLT5/PMA1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)
/IO03: J1.9, U1.24 (AN11/CVD11/C1IN2-/FLT4/PMA12/RC11)
/IO04: J1.10, U1.22 (OA3IN-/AN7/CVD7/C3IN1-/C4IN1-/RPC1/PMA7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)
/IO05: J1.11, U1.63 (RPB13/PWM8H/PWM2L/CTPLS/PMD3/RB13)
/IO06: J1.12, U1.62 (RPB12/PWM2H/PMD2/RB12)
/IO07: J1.13, U1.61 (RPB11/PWM9H/PWM3L/PMD1/RB11)
/IO08: J1.14, U1.60 (RPB10/PWM3H/PMD0/RB10)
/IO09: J1.15, U1.17 (PGC1/OA1IN+/AN4/C1IN1+/C1IN3-/C2IN3-/RP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)
/IO10: J1.16, U1.64 (TDO/PWM4H/PMD4/RA10)
/MC_IU_SEN: J2.24, U1.33 (OA5IN+/DAC1/AN24/CVD24/C5IN1+/C5IN3-/RP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)
/MC_IV_SEN: J2.26, U1.31 (TDI/DAC3/AN26/CVD26/RPA8/SDA2/PMA9/RA8)
/MC_PWM_UH: J2.19, U1.53 (TRD2/RPD5/PWM12H/PMRD/RD5)
/MC_PWM_UL: J2.20, U1.54 (TRD3/RPD6/PWM12L/RD6)
/MC_PWM_VH: J2.17, U1.52 (TRD1/RPC8/PWM5H/PMWR/RC8)
/MC_PWM_VL: J2.18, U1.55 (RPC9/PWM11H/PWM5L/RC9)
/MC_PWM_WH: J2.15, U1.50 (TRCLK/RPC6/PWM6H/RC6)
/MC_PWM_WL: J2.16, U1.51 (TRD0/RPC7/PWM12H/PWM6L/RC7)
/MC_TEMP_SEN: J2.21, U1.49 (TMS/OA5IN-/AN27/CVD27/LVDIN/C5IN1-/RPB9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)
/MC_VR_DIV: J2.22, U1.30 (AN15/CVD15/RPE15/FLT8/PMA0/RE15)
/MC_VU_DIV: J2.23, U1.16 (PGC3/OA1OUT/VREF+/AN3/C1IN4-/C4IN2-/RPB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)
/MC_VV_DIV: J2.25, U1.23 (OA3IN+/AN8/CVD8/C3IN1+/C3IN3-/RPC2/FLT3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)
/PFC_IA_SEN: J1.26, U1.13 (OA2OUT/AN0/C2IN4-/C4IN3-/RPA0/RA0)
/PFC_IB_SEN: J1.24, U1.14 (OA2IN+/AN1/C2IN1+/RPA1/RA1)
/PFC_PWM_A: J1.20, U1.2 (RPB14/PWM1H/VBUSON1/PMD6/RB14)
/PFC_PWM_B: J1.18, U1.3 (RPB15/PWM7H/PWM1L/PMD7/RB15)
/PFC_PWM_ENA: J1.19, U1.11 (AN10/CVD10/RPA12/RA12)
/PFC_PWM_ENB: J1.17, U1.12 (AN9/CVD9/RPA11/RA11)
/PGC: J2.4, U1.44 (PGC2/RPB6/SCL3/SCK2/PMA15/RB6)
/PGD: J2.2, U1.43 (PGD2/RPB5/SDA3/USBID1/RB5)
/RTS2: J2.11, U1.32 (FLT15/RPB4/SCL2/PMA8/RB4)
/RXD1: J2.7, U1.47 (SOSCI/RPC13/RC13)
/RXD2: J2.9, U1.48 (SOSCO/T1CK/RPB8/RB8)
/SLED: R1.2, U1.42 (RD8)
/TXD1: J2.8, U1.46 (OA5OUT/AN25/CVD25/C5IN4-/RPB7/SCK1/INT0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)
/TXD2: J2.10, U1.45 (DAC2/AN48/CVD48/RPC10/PMA14/PMCS/RC10)
/USB_N: J2.3, U1.36 (D-)
/USB_P: J2.5, U1.37 (D+)
/VAC_DIV: J1.21, U1.18 (PGD1/OA1IN-/AN5/CTCMP/C1IN1-/RTCC/RPB3/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)
/VBUS: J2.1, U1.34 (VBUS)
/VDC_DIV: J1.23, U1.21 (OA3OUT/AN6/CVD6/C3IN4-/C4IN1+/C4IN4-/RP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)
/~INV_FLT: J2.13, U1.59 (RPF1/PWM11L/RF1)
/~MCLR: C1.2, J2.6, R3.1, U1.7 (~MCLR)
/~PFC_FLT: J1.22, U1.1 (TCK/RPA7/PWM10H/PWM4L/PMD5/RA7)
AGND: C12.1, C13.1, J1.1, J1.2, U1.20 (AVSS)
AVDD: C12.2, C13.2, J1.3, J1.4, U1.19 (AVDD)
GND: C1.1, C10.1, C19.1, C20.1, C21.1, C22.1, C23.1, C24.1, C25.1, C26.1, C27.1, C28.1, D1.K, D2.K, J1.5, J1.6, J2.29, J2.30, U1.9 (VSS1), U1.25 (VSS2), U1.41 (VSS3), U1.56 (VSS4), U2.2 (GND1), U2.4 (GND2)
unnamed: D1.A, R1.1
unnamed: D2.A, R2.1
unnamed: C19.2, U1.39 (OSCI/CLKI/AN49/CVD49/RPC12/RC12), U2.1 (X1)
unnamed: C20.2, U1.40 (OSCO/CLKO/RPC15/RC15), U2.3 (X2)

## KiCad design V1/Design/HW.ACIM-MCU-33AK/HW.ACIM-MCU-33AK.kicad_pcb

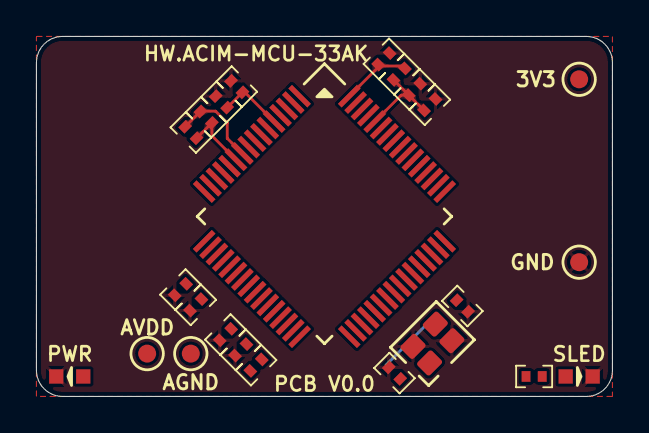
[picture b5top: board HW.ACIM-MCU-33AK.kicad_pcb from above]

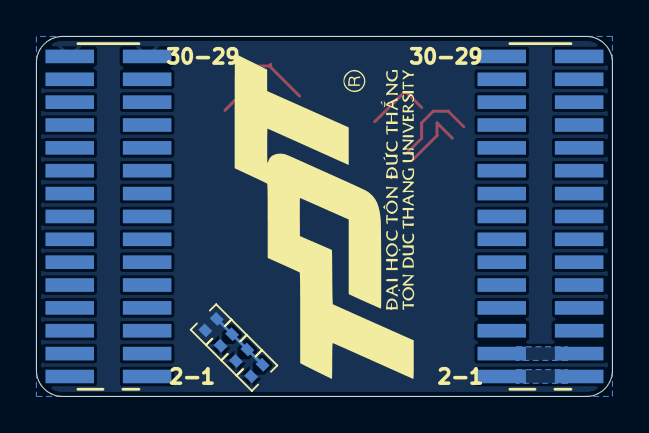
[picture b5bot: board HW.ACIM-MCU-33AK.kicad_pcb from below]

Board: 4 copper layers, 32.0 x 20.0 mm, 30 parts (6 on the bottom side), 19 nets.

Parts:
C1, C19, C20: 22pF; CAP0402
C2, C3, C13, C22, C24, C26, C28: 10uF; CAP0402
C4, C10, C12, C21, C23, C25, C27: 100nF; CAP0402
D1: SLED; LED0603
D2: PWR; LED0603
J1, J2: HEADER 2x15POS; HD-2x15x1.27-SMD
R1, R2: 1K; RES0402
R3: 10K; RES0402
TP1: GND; TP1MM
TP2: 3V3; TP1MM
TP3: AGND; TP1MM
TP4: AVDD; TP1MM
U1: dsPIC33AKxxxMC106; TQFP64_10x10_MCHP
U2: 12MHz; SMD4-2520

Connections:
+3V3: C2.2, C3.2, C4.2, C10.2, C12.2, C13.2, C21.2, C22.2, C23.2, C24.2, C25.2, C26.2, J2.27, J2.28, R2.2, R3.2, TP2.1, U1.5 (VDD), U1.19 (VDD), U1.26 (VDD), U1.40 (VDD), U1.48 (VDD), U1.60 (VDD)
/MC_PWM_UH: J2.19, U1.53 (TDO/RP51/PWM1H/IOMD4/RD2)
/MC_PWM_UL: J2.20, U1.54 (TDI/RP52/PWM1L/IOMD5/RD3)
/MC_PWM_VH: J2.17, U1.51 (RP49/PWM2H/IOMD2/RD0)
/MC_PWM_VL: J2.18, U1.52 (TCK/RP50/PWM2L/IOMD3/RD1)
/MC_PWM_WH: J2.15, U1.43 (PGD3/RP36/PWM3H/IOMD0/RC3)
/MC_PWM_WL: J2.16, U1.44 (RP37/PWM3L/IOMD1/RC4)
/PGC: J2.4, U1.28 (PGC1/AD2AN5/CMP2C/ISRC1/IBIAS1/RP21/SCL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)
/PGD: J2.2, U1.27 (PGD1/AD1AN5/CMP1C/ISRC0/IBIAS0/RP20/SDA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)
/SCL: J1.11, U1.61 (RP53/PCI22/RD4)
/SDA: J1.12, U1.55 (RP54/ASCL1/RD5)
/~MCLR: C1.2, J2.6, R3.1, U1.64 (~MCLR)
AGND: C27.1, C28.1, J1.1, J1.2, TP3.1, U1.10 (AVSS)
AVDD: C27.2, C28.2, J1.3, J1.4, TP4.1, U1.11 (AVDD)
GND: C1.1, C2.1, C3.1, C4.1, C10.1, C12.1, C13.1, C19.1, C20.1, C21.1, C22.1, C23.1, C24.1, C25.1, C26.1, D1.K, D2.K, J1.5, J1.6, J2.29, J2.30, TP1.1, U1.4 (VSS), U1.18 (VSS), U1.25 (VSS), U1.39 (VSS), U1.47 (VSS), U1.59 (VSS), U2.2 (GND1), U2.4 (GND2)
unnamed: D1.A, R1.1
unnamed: D2.A, R2.1
unnamed: C20.2, U1.38 (OSCI/CLKI/RP34/IOMF6/RC1), U2.3 (X2)
unnamed: C19.2, U1.37 (OSCO/CLKO/RP33/IOMF5/RC0), U2.1 (X1)

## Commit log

2024-09-25 Initialize
2024-09-25 V0 production files
2024-09-25 V1 schematic
2024-09-30 MCU PIM schematic
2024-10-04 MCU PIM schematic update 1
2024-10-11 HW.ACIM-INV_REV0.0 firmware configuration
2024-10-12 Add FwLib sub-module
2024-10-13 Add sys_debug
2024-10-13 Add coreTimer, change tmr1 periode, add SixStep lib
2024-10-13 MCU PIM schematic update 2
2024-10-16 Add 3P PWM, PwrMoni
2024-10-17 Update PwrMoni, add Encoder lib
2024-10-25 MCU PIM schematic update 3
2024-10-30 MCU PIM schematic update 4
2024-11-04 MCU PIM schematic update 5
2024-11-05 MCU PIM schematic update 6
2024-11-07 MCU PIM schematic update 7
2024-11-08 MCU PIM schematic update 8
2024-11-10 HW.ACIM-MCU-32MK Rev0.0
2024-11-13 HW.ACIM-MCU-33AK schematic rev0.0
2024-11-23 V1 schematic update 1
2024-11-23 V1 schematic update 2
2024-11-26 V1 schematic update 3
2024-11-28 V1 schematic update 4
2024-11-28 V1 schematic update 5
2024-12-01 V1 schematic update 6
2024-12-02 V1 schematic update 7
2024-12-03 V1 schematic update 8
2024-12-03 V1 schematic update 9
2024-12-04 V1 schematic update 10
2024-12-06 HW.ACIM-MCU-E70 schematic
2024-12-10 HW.ACIM-MCU-E70 schematic update 1
2024-12-11 HW.ACIM-MCU-E70 schematic update 2
2024-12-16 V1 schematic update 11
2024-12-17 V1 schematic update 12
2024-12-17 V1 schematic update 13
2024-12-18 V1 schematic update 14
2024-12-19 V1 schematic update 15
2024-12-19 V1 schematic update 16
2024-12-21 V1 schematic update 17
2024-12-22 V1 schematic update 18
2024-12-23 V1 schematic update 19
2024-12-29 V1 schematic update 20
2024-12-30 V1 schematic update 21
2025-01-01 V1 schematic update 22
2025-01-02 V1 schematic update 23
2025-01-03 V1 schematic update 24
2025-01-05 V1 schematic update 25
2025-01-06 V1 schematic update 26
2025-01-07 V1 schematic update 27
2025-01-08 V1 schematic update 28
2025-01-09 V1 schematic update 29
2025-01-10 V1 schematic update 30
2025-01-12 V1 layout
2025-01-19 HW.ACIM-INV-V1.0
2025-01-21 HW.ACIM-MCU-32MK update net name
2025-03-28 HW.ACIM-MCU-32MK update schematic in production
2025-04-17 Label & Case
2025-04-23 Encoder emulator
2025-04-23 Update schematic
2025-05-02 Sine PWM & SV PWM flowchart
2025-05-02 V2 diagram & schematic
2025-05-06 HW.ACIM-ADAP schematic
2025-05-06 HW.ACIM-ADAP remove
2025-05-06 V2 diagram & schematic update 1
2025-05-07 V2 diagram & schematic update 2
2025-05-09 V2 diagram & schematic update 3
2025-06-06 V2 diagram & schematic update 4
2025-06-14 HW.ACIM-MCU-ADAP schematic
2025-06-15 HW.ACIM-MCU-ADAP schematic update 1
2025-06-16 HW.ACIM-MCU-ADAP schematic update 2
2025-06-16 HW.ACIM-MCU-ADAP schematic update 3
2025-06-18 HW.ACIM-MCU-ADAP schematic update 4
2025-06-19 HW.ACIM-MCU-ADAP schematic update 5
2025-06-19 HW.ACIM-MCU-ADAP layout & production
2025-06-26 HW.ACIM-MCU-ADAP_V0.0
2025-07-08 HW.ACIM-MCU-ADAP_V0.0 update bom
2025-07-14 HW.ACIM-MCU-ADAP_V0.0 update ibom
2025-09-06 IPM test
2025-09-06 IPM test update
2025-10-01 Update Adaptor
